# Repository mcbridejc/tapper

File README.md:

# Tapper

A flexible way to build well-packaged touch-screen based devices with 
STM32 nucleo-32 boards. 

## Introduction

I wanted a quick and easy way to bring up any kind of touch screen based 
device that wasn't a one-off jumble of wires and/or breadboards.
My main requirements are that it needs a case, and it needs to be connecterized. 
I wanted to keep some flexibility though, because you can't quite predict which 
pins you need to wire out to which connectors next time, and you might need a 
bit of extra circuitry. 

On tapper, the connector IOs are connected only to test points. 
The MCU pins are also wired out to test points. To customize for a particular 
application, just solder jumper wires to connect as neded. 
There's also a small amount of 0.1" pitch hole array for prototyping; enough 
to fit a couple chips and discretes, e.g. using SMT to DIP adapters.

PDF schematic can be found [here](pcb/Tapper_rev2_schematic.pdf).

Bill of materials can be found [here](pcb/BOM.xlsx).

Gerbers can be found under github releases, if you want to build one!

## Powering 

The Tapper has a 5.5x2.1mm barrel connector for power input (7V min, up to about 
12-ish V<sup>[1](#maxvolts)</sup>), or, optionally it can be powered via the USB connector if you
don't need any voltage higher than 5V. 
For my initial application I needed a higher voltage for motor control, so
the tapper includes a linear regulator to generare the 5V input for the nucleo.
Thanks to the diode-or on the nucleo-32 board, it is safe to provide both USB 
power and an extra VIN. 

## Connectors

There are three 6-pin JST SH connectors. [Pre-made pigtails](https://www.digikey.com/en/products/detail/trinamic-motion-control-gmbh/CABLE-PH06/9381902) 
can be used to connect to these. Each connector has a ground pin, a power pin 
which can be connected to 3.3V, 5V, or VIN -- selected by solder bridge -- and
four IO pins which are connected to testpoints. These can be connected by 
wires soldered to either the MCU breakout testpoints or to 
a circuit on the prototype pad array.

## STM32 Development Board

Tapper is designed for the [Nucleo-G431KB](https://www.st.com/en/evaluation-tools/nucleo-g431kb.html),
but since all of the Nucleo-32 boards have a compatible pinout -- at least 
I'm pretty sure they do, double check -- it should be easy to use a different
family of STM32 MCU. The ST Nucleo boards come with a built-in ST-LINK USB
programmer/debugger, which also provides a virtual COM port connected to the
USART on your target device.

### Nucleo board modifications

**Important: You probably need to modify your Nucleo board!**

Remove SB2 and SB3. These short PA15 to PA6 and PB7 to PA6 -- why ST thought
it was a good idea to ship development boards with jumpers shorting their 
IOs is beyond me, but removing them is the first thing I do on every nucleo 
board.

Short SB11. This connects PF1 to the IO header, and is needed to drive the 
display DC pin. Without shorting this solder bridge, the display will not
update.

## Enclosure

The enclosure can be 3D printed. Heated threaded inserts are used to provide
solid mounting points for the electronicson the top cover. See the 
[Bill of Materials](pcb/BOM.xls). It uses flexible retaining clips to hold
the two parts of the enclosure together, and this works....OK. If the print 
isn't dialed in just right, the top cover might not sit perflectly tight; 
functional but disappointing. At some point, I may redesign it to use some 
longer screws that go all the way through the enclosure. It was the first 
time I tried printing such a thing, and it was a worthwhile experiment, anyway.

### Top Model

[3D Model - STEP](enclosure/tapper_enclosure_top.step)

[3D Model - STL](enclosure/tapper_enclosure_top.stl)

### Bottom Model

[3D Model - STEP](enclosure/tapper_enclosure_bottom.step)

[3D Model - STL](enclosure/tapper_enclosure_bottom.stl)

## Example Software

This [spincoater controller](https://github.com/mcbridejc/spincoater-controller) project uses the Tapper board, and provides an
example software project using the [modm](https://modm.io) C++ peripheral library, which
I highly recommend for STM32 projects.

## Photos

## Revision History

### Revision 2 (Nov 2020)

Fix a few mistakes, including: 

- Add pull-up to display reset pin
- Power connection points labeled wrong in silkscreen (3.3V and VIN swapped, yikes)
- One mounting hole position off by 0.5mm

### Revision 1 (Oct 2020)

First prototype design. 

# Footnotes

<b id="maxvolts">1:</b>The max voltage will be limited by the thermal dissipation of the 
linear regulator, and will depend on how much power is drawn from the 5V rail. If 
it gets too hot to touch, it might be time to consider lowering your input voltage!

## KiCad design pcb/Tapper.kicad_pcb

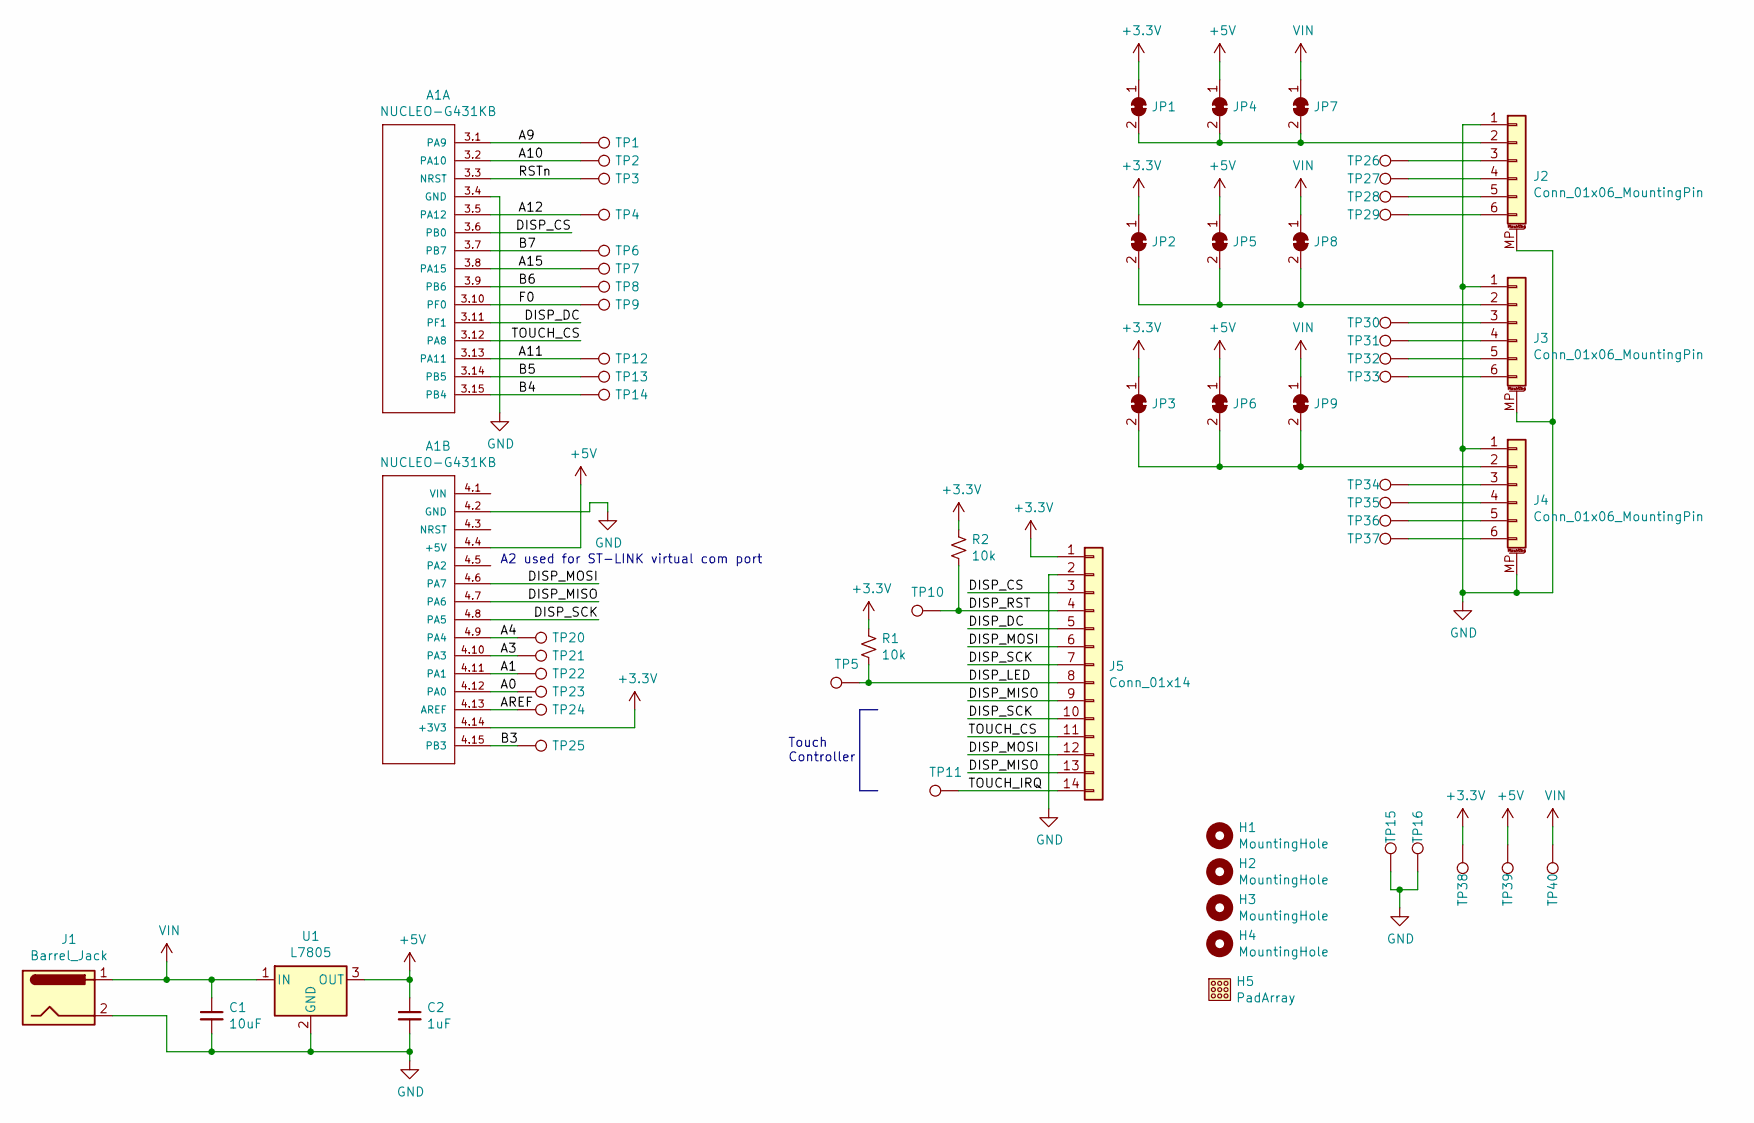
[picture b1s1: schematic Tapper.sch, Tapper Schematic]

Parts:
A1: NUCLEO-G431KB; MODULE_NUCLEO-32
C1: 10uF; C_1206_3216Metric_Pad1.42x1.75mm_HandSolder; Mfg Part Number CL31A106KBHNNNE
C2: 1uF; C_0805_2012Metric_Pad1.15x1.40mm_HandSolder; Mfg Part Number CL21B105KAFNNNG
H1, H2, H3, H4: MountingHole; SpacerPad
H5: PadArray; ProtoArray_10x10_2.54mm
J1: Barrel_Jack; BarrelJack_Horizontal
J2, J3, J4: Conn_01x06_MountingPin; JST_PH_S6B-PH-SM4-TB_1x06-1MP_P2.00mm_Horizontal
J5: Conn_01x14; PinHeader_1x14_P2.54mm_Vertical
JP1, JP2, JP3, JP4, JP5, JP6, JP7, JP8, JP9: SolderJumper_2_Bridged; SolderJumper-2_P1.3mm_Open_TrianglePad1.0x1.5mm
R1, R2: 10k; R_1206_3216Metric_Pad1.42x1.75mm_HandSolder
TP1, TP2, TP3, TP4, TP5, TP6, TP7, TP8, TP9, TP10, TP11, TP12, TP13, TP14, TP15, TP16, TP20, TP21, TP22, TP23, TP24, TP25, TP26, TP27, TP28, TP29, TP30, TP31, TP32, TP33, TP34, TP35, TP36, TP37, TP38, TP39, TP40: TP; SolderPoint
U1: L7805; TO-263-2; Mfg Part Number L7805ABD2T-TR

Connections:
+3V3: A1.4.14 (+3V3), J5.1, JP1.1 (A), JP2.1 (A), JP3.1 (A), R1.1, R2.1, TP38.1
+5V: A1.4.4 (+5V), C2.1, JP4.1 (A), JP5.1 (A), JP6.1 (A), TP39.1, U1.3 (OUT)
/A0: A1.4.12 (PA0), TP23.1
/A1: A1.4.11 (PA1), TP22.1
/A3: A1.4.10 (PA3), TP21.1
/A4: A1.4.9 (PA4), TP20.1
/A9: A1.3.1 (PA9), TP1.1
/A10: A1.3.2 (PA10), TP2.1
/A11: A1.3.13 (PA11), TP12.1
/A12: A1.3.5 (PA12), TP4.1
/A15: A1.3.8 (PA15), TP7.1
/AREF: A1.4.13 (AREF), TP24.1
/B3: A1.4.15 (PB3), TP25.1
/B4: A1.3.15 (PB4), TP14.1
/B5: A1.3.14 (PB5), TP13.1
/B6: A1.3.9 (PB6), TP8.1
/B7: A1.3.7 (PB7), TP6.1
/DISP_CS: A1.3.6 (PB0), J5.3
/DISP_DC: A1.3.11 (PF1), J5.5
/DISP_LED: J5.8, R1.2, TP5.1
/DISP_MISO: A1.4.7 (PA6), J5.9, J5.13
/DISP_MOSI: A1.4.6 (PA7), J5.6, J5.12
/DISP_RST: J5.4, R2.2, TP10.1
/DISP_SCK: A1.4.8 (PA5), J5.7, J5.10
/F0: A1.3.10 (PF0), TP9.1
/RSTn: A1.3.3 (NRST), TP3.1
/TOUCH_CS: A1.3.12 (PA8), J5.11
/TOUCH_IRQ: J5.14, TP11.1
GND: A1.3.4 (GND), A1.4.2 (GND), C1.2, C2.2, J1.2, J2.1, J2.MP (MountPin), J3.1, J3.MP (MountPin), J4.1, J4.MP (MountPin), J5.2, TP15.1, TP16.1, U1.2 (GND)
unnamed: J2.2, JP1.2 (B), JP4.2 (B), JP7.2 (B)
unnamed: J2.3, TP26.1
unnamed: J2.4, TP27.1
unnamed: J2.5, TP28.1
unnamed: J2.6, TP29.1
unnamed: J3.2, JP2.2 (B), JP5.2 (B), JP8.2 (B)
unnamed: J3.3, TP30.1
unnamed: J3.4, TP31.1
unnamed: J3.5, TP32.1
unnamed: J3.6, TP33.1
unnamed: J4.2, JP3.2 (B), JP6.2 (B), JP9.2 (B)
unnamed: J4.3, TP34.1
unnamed: J4.4, TP35.1
unnamed: J4.5, TP36.1
unnamed: J4.6, TP37.1
VIN: C1.1, J1.1, JP7.1 (A), JP8.1 (A), JP9.1 (A), TP40.1, U1.1 (IN)

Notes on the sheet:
A2 used for ST-LINK virtual com port
Touch Controller

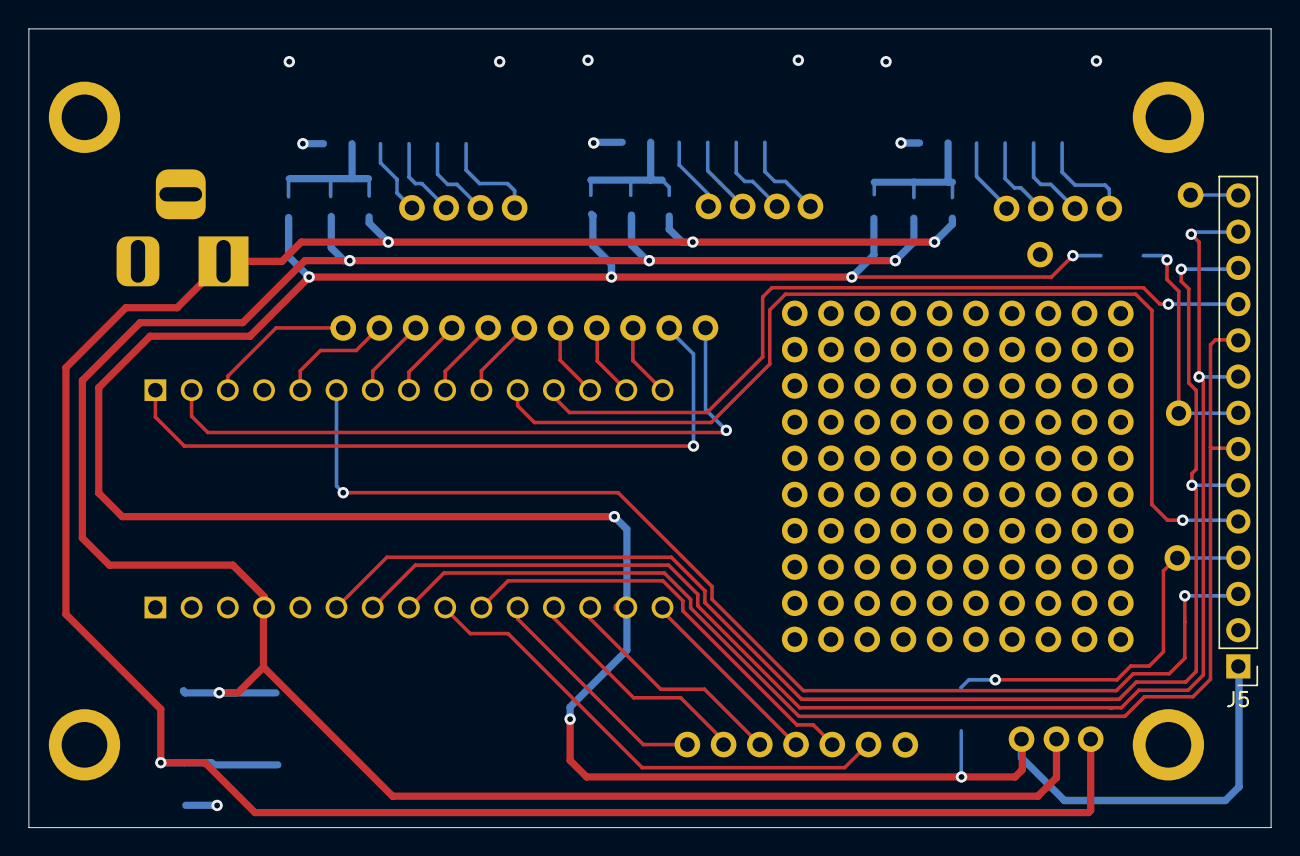
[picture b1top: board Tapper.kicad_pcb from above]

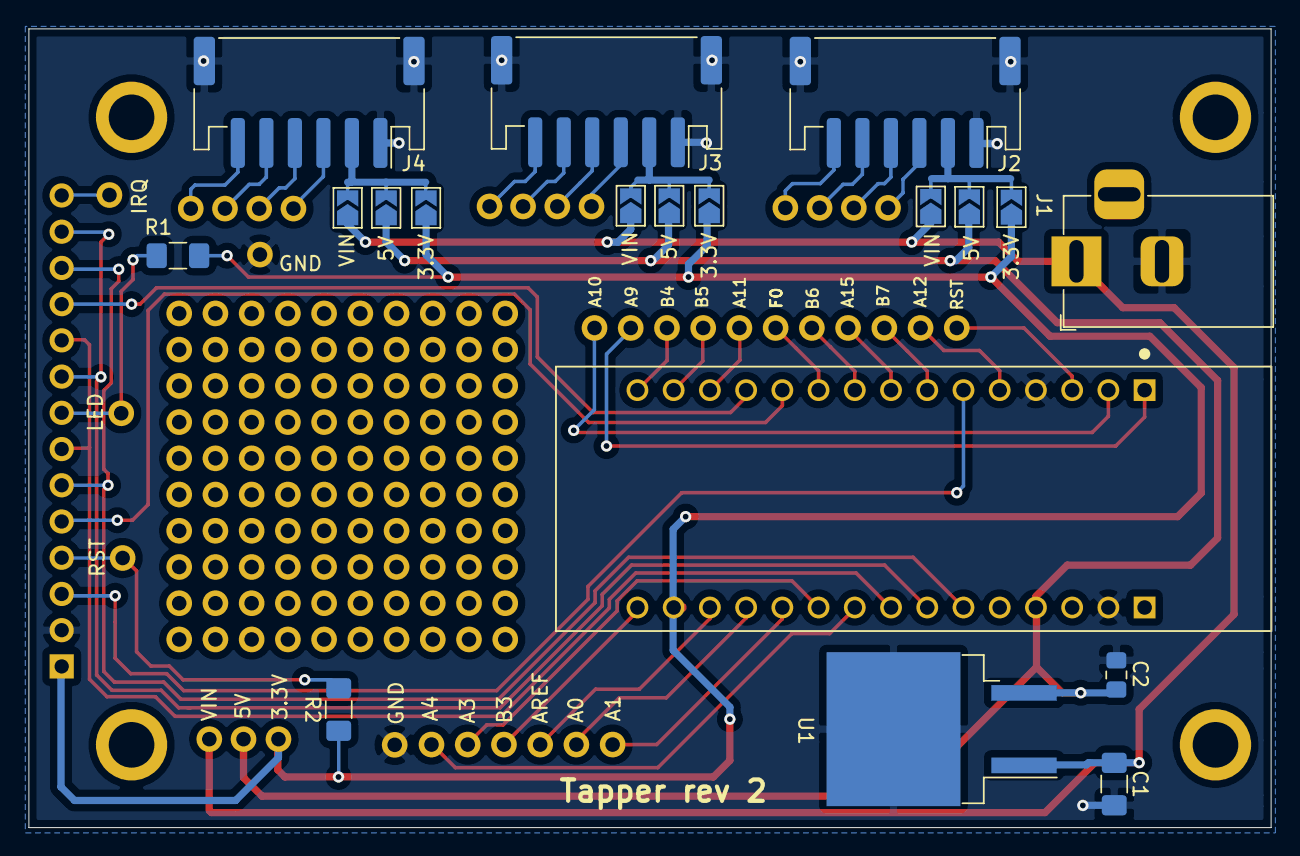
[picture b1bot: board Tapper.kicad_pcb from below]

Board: 2 copper layers, 87.1 x 56.0 mm, 62 parts (19 on the bottom side), 45 nets.

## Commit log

2020-11-15 Rev 1 PCB files
2020-11-15 Add PDF schematic for rev1
2020-11-15 Fix errors in rev1
2020-11-19 Add enclosure models
2020-11-19 Add rev2 gerbers
2020-11-19 Add rev2 schematic PDF
2020-11-19 Add README and photos
2020-11-19 Add LICENSE file
2020-11-19 Add note about nucleo board modifications
